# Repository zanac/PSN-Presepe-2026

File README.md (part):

<p align="center"><b>🇬🇧 English</b> &nbsp;·&nbsp; <a href="README.it.md">🇮🇹 Italiano</a></p>

# PSN-Presepe

Arduino Mega 2560 controller for a modular 12 V nativity scene (*presepe*).

It runs a day/night cycle: **GIORNO → TRAMONTO → CREPUSCOLO → NOTTE → ALBA** (day → sunset → dusk → night → dawn). The cycle drives:

- three analog 12 V RGB strips: main sky, sunset side and dawn side;
- two addressable WS2811 chains of twinkling stars, STELLE_01 and STELLE_02 (for example two zones of the sky);
- 16 relays for motors, pumps and lamps.

Every scenography parameter can be changed from a `PRESEPE.INI` file on a microSD card, read at power-on.

This repository holds the complete project, for both board revisions:

- the PCB (KiCad), with the scripts that generate and verify it;
- manufacturing files ready for a turnkey assembler;
- the firmware, with its tests;
- wiring documentation for building the controller on a breadboard without the PCB.

> **Status.** The Rev D PCB was ordered from PCBWay (turnkey assembly, see [manufacturing/pcbway-order-2026-10-04](hardware/rev-d/manufacturing/pcbway-order-2026-10-04/README.md)) and the assembled boards have been tested: everything works. **Rev E** (small fixes plus a status LED and test points, same size and connectors, same firmware) is being designed in [`hardware/rev-e`](hardware/rev-e); it has not been ordered yet. See [Rev E](#rev-e-next-revision).

**Two board releases.** Both use the same firmware, the same `PRESEPE.INI` and the same terminals, so the rest of this README applies to either:

| Release | Folder | State | Use it for |
|---|---|---|---|
| **Rev D** | [`hardware/rev-d`](hardware/rev-d) | ordered, assembled and tested: works | the boards already built; reference for reorders as they are |
| **Rev E** | [`hardware/rev-e`](hardware/rev-e) | designed and verified, not ordered yet | the next order: buzzer footprint for the CEM-1203(42), polarised C1, 8 mil spacing, status LED, test points |

To flash the firmware (plain Mega or Mega + WiFi) see [Step by step with the Arduino IDE](#step-by-step-with-the-arduino-ide).

## Contents

1. [Repository layout](#1-repository-layout)
2. [How the controller works](#2-how-the-controller-works)
3. [The Rev D board](#3-the-rev-d-board)
4. [Board connectors (terminal pinout)](#4-board-connectors-terminal-pinout)
5. [Arduino Mega pin map](#5-arduino-mega-pin-map)
6. [Power, currents and fusing](#6-power-currents-and-fusing)
7. [Wiring the loads](#7-wiring-the-loads)
8. [Breadboard / prototype build without the PCB](#8-breadboard--prototype-build-without-the-pcb)
9. [Firmware](#9-firmware)
10. [SD-card configuration (PRESEPE.INI)](#10-sd-card-configuration-presepeini)
11. [PCB design rules and verification](#11-pcb-design-rules-and-verification)
12. [Ordering the board](#12-ordering-the-board)
13. [Rebuilding everything](#13-rebuilding-everything)
14. [Known limitations and open points](#14-known-limitations-and-open-points)
15. [Safety](#15-safety)
16. [Revision history](#16-revision-history)

---

## 1. Repository layout

```
build.sh                        one-command rebuild + verification of every PCB revision and the firmware
hardware/
  rev-d/                        Rev D, the board ordered from PCBWay (frozen; rebuilds to identical Gerbers)
    build.sh                    rebuild + verification of this revision only
    build/
      scripts/                  PCB generator, router glue, DRC, independent checkers, exporters
      data/                     reference netlist/pad data and the stored routing session (routing.ses)
      lib/PSN_RevD.pretty/      custom footprints (Arduino Mega shield, JLC tooling hole)
    kicad/                      KiCad 7 project: board, rules, schematic (+PDF), local footprint library
    manufacturing/              Gerbers, drill maps, BOMs, pick-and-place files, assembly instructions, 1:1 print
      pcbway-order-2026-10-04/  FROZEN copy of the files actually sent to PCBWay (+ SHA256SUMS, order notes)
    previews/                   renders of the board (KiCad layers and photo-style Gerber renders)
    reports/                    DRC, independent board/Gerber checks, schematic parity, footprint checks
  rev-e/                        Rev E, the next revision (same layout as rev-d; not ordered yet)
firmware/
  PSN-Presepe/                  the whole firmware in one sketch (PSN-Presepe.ino), example PRESEPE.INI, prebuilt HEX, Windows flasher
  PSN-Presepe-WiFi/             firmware of the ESP8266 on a "Mega + WiFi R3" board (web pages, OTA), prebuilt BIN
  web/                          pannello.html, the control panel served by the ESP8266
  tools/                        fw_compile.sh, esp_compile.sh, flash.sh (Linux/macOS), build_web.py, embed_ini.py, run_tests.sh, host tests
    e2e/                        end-to-end test: real Mega link code + real ESP sketch over a lossy simulated serial line
simulation/                     Wokwi simulation of the Rev D wiring (diagram, custom RGB chip, bundle script)
simulation_web/                 browser simulator of the PRESEPE.INI light cycle (open index.html)
demo/                           the WiFi web pages with a simulated board, to try them without hardware (generated)
.github/workflows/firmware.yml  CI: host tests + compile of both firmwares
```

Everything in `hardware/rev-d/kicad/`, `manufacturing/` (except the frozen order folder), `previews/` and `reports/` is generated by `hardware/rev-d/build.sh`. Edit the scripts, not the generated files (see [section 13](#13-rebuilding-everything)).

## 2. How the controller works

| Element | Hardware | Behaviour |
|---|---|---|
| **CIELO** (sky) | 12 V common-anode RGB strip, 3 PWM MOSFET channels | Warm day light, full white at mid-day, fades to dark at night, warm dawn glow |
| **TRAMONTO** (sunset, left) | 12 V RGB strip, 3 PWM channels | Orange/red swell during sunset only, completely off otherwise |
| **ALBA** (dawn, right) | 12 V RGB strip, 3 PWM channels | Lighter warm swell during dawn only |
| **STELLE_01** (stars) | 12 V WS2811 chain on D5 (default 50 pixels) | Random stars appear at dusk, twinkle individually at night, fade at dawn |
| **STELLE_02** (stars) | 12 V WS2811 chain on D8 (default 50 pixels) | Same behaviour as STELLE_01, with its own settings: a second zone of the sky |
| **Relays 1–16** | Omron G5Q-1, potential-free COM/NO/NC contacts | Switched on/off at programmable points of each phase |
| **Controls** | START/STOP, NEXT, TEST buttons, speed potentiometer | Pause/resume, jump to next phase, output test, choose 1 of 3 cycle lengths |
| **OLED** | 0.96" SSD1306 128×64 I2C | Phase, progress, cycle length, SD status, test steps (optional) |
| **Buzzer** | passive piezo / magnetic buzzer | Key beeps and a start-up melody (optional) |
| **microSD** | push-push slot on the board edge | `PRESEPE.INI` with all parameters; without a card the built-in defaults are used |

Default phase boundaries, as % of the cycle: TRAMONTO 40 %, CREPUSCOLO 50 %, NOTTE 55 %, ALBA 85 %. ALBA ends at 100 %, where the next GIORNO begins.

Default cycle lengths: 1, 3 or 5 minutes, chosen by the potentiometer.

## 3. The Rev D board

- 300 × 180 mm, 2 layers, FR-4 1.6 mm, **2 oz copper**, HASL, tented vias.
- The board is a shield: it plugs onto an **Arduino Mega 2560 R3**, which sits underneath. The Mega headers are mounted on the bottom side.
- All field wiring goes through **5.08 mm screw terminals** on the board edges.
- Single **12 V** input. The Mega is powered through VIN, and the microSD gets its own 3.3 V LDO.

| Block | Parts |
|---|---|
| 12 V input | J1, bulk capacitor C1 470 µF |
| RGB drivers | 9 × IRLZ44N logic-level MOSFETs (Q1–Q9), 100 Ω gate resistor + 100 kΩ pull-down each, low-side switching |
| Relay drivers | 2 × ULN2803A (U1, U2), freewheel diodes inside (COM pin to +12 V), 16 × Omron G5Q-1 DC12 |
| Relay outputs | JR1–JR16, 3-pole COM / NO / NC, isolated 230 V AC area (see [section 11](#11-pcb-design-rules-and-verification)) |
| microSD | Hirose DM3AT-SF-PEJM5 push-push with card detect, AMS1117-3.3 LDO from +12 V, 74LVC125A level shifter for SCK/MOSI/CS, 10 kΩ pull-ups |
| Buzzer | BZ1 (passive, 7.6 mm pitch) through 220 Ω from D6 |
| Controls / OLED / pot | Terminals only; the parts are off-board |

| Top (copper + silk) | Bottom (copper + silk) |
|---|---|
|  |  |

Assembly drawing: [previews/PSN-Presepe-Mega-RevD-assembly.png](hardware/rev-d/previews/PSN-Presepe-Mega-RevD-assembly.png). Schematic: [kicad/PSN-Presepe-Mega-RevD-schematic.pdf](hardware/rev-d/kicad/PSN-Presepe-Mega-RevD-schematic.pdf). The schematic is generated from the board and uses global net labels, so read it together with the tables below.

### Rev E (next revision)

Rev E keeps the Rev D board outline, connectors, placement and pin map, so the same firmware runs on both. Files: [`hardware/rev-e`](hardware/rev-e) (`kicad/`, `manufacturing/`, `previews/`, `reports/`, rebuilt by `hardware/rev-e/build.sh`). Status: designed and verified by the same automated checks as Rev D, **not ordered yet**.

| Change | Why |
|---|---|
| BZ1 footprint with **6.5 mm** pin pitch (local footprint `Buzzer_12x9.5RM6.5`) | fits the buzzer PCBWay sources, Same Sky CEM-1203(42); on Rev D they had to bend its pins |
| C1 on a **polarised** footprint (`CP_Radial_D10.0mm_P5.00mm`: square + pad, "+" on the silkscreen) | Rev D had two identical round pads |
| Minimum copper clearance **0.22 mm** (Rev D rule 0.20 mm, 0.202 mm measured) | PCBWay asks for 8 mil (0.2032 mm) with 2 oz copper |
| **Status LED** D1 (green, 3 mm) with RLED 1 kΩ (0805) on Mega D13, top-left next to the microSD | shows at a glance whether the controller runs, is paused, in TEST or STOP (see [Operation](#operation)) |
| **Test points** TP1–TP5 in a row: +12V, GND, +5V, GND, +3V3 (plated 2 mm pads, no part) | measure the supplies with a meter without looking for a pin; a slipping probe can only short a rail to GND, never 12 V onto 5 V |
| No vias above the Mega USB-B socket (rule area in the board, used by the router and by KiCad DRC) | was only checked afterwards on Rev D |
| Star terminals named **J_STELLE_01** / **J_STELLE_02** (silkscreen STELLE_01 / STELLE_02, nets `D5_STELLE_01_DATA` / `D8_STELLE_02_DATA`) | the firmware drives two identical star chains; Rev D still says STELLE / CASETTE |

The routing is new (Freerouting), stored in `hardware/rev-e/build/data/routing.ses` so that the build is reproducible. Before ordering, print the 1:1 PDF and check the real buzzer, C1 and LED on it ([Before ordering a new revision](#before-ordering-a-new-revision)).

## 4. Board connectors (terminal pinout)

Pin 1 is the square pad. The function of each pin is also printed on the silkscreen next to every terminal.

### Bottom edge, left to right

| Terminal | Pin 1 | Pin 2 | Pin 3 | Pin 4 | Use |
|---|---|---|---|---|---|
| **J1** POWER 12V | +12 V | GND | | | Power supply input |
| **J_OLED** | +5 V (Mega) | GND | SDA (D20) | SCL (D21) | OLED display |
| **J_START** | D22 | GND | | | START/STOP button (normally open) |
| **J_NEXT** | D23 | GND | | | NEXT button (normally open) |
| **J_TEST** | D24 | GND | | | TEST button (normally open) |
| **J_POT** | +5 V (Mega) | A0 (wiper) | GND | | External 10 kΩ linear potentiometer |
| **J_CIELO** | +12 V | R− | G− | B− | Sky RGB strip (common anode) |
| **J_TRAMONTO** | +12 V | R− | G− | B− | Sunset RGB strip |
| **J_ALBA** | +12 V | R− | G− | B− | Dawn RGB strip |
| **J_STELLE** (Rev D) / **J_STELLE_01** (Rev E) | +12 V | GND | DATA (D5) | | WS2811 chain STELLE_01 |
| **J_CASETTE** (Rev D) / **J_STELLE_02** (Rev E) | +12 V | GND | DATA (D8) | | WS2811 chain STELLE_02 (the Rev D silkscreen still says CASETTE) |

### Top and right edges (relay area)

| Terminal | Pin 1 | Pin 2 | Pin 3 |
|---|---|---|---|
| **JR1 … JR16** | COM | NO (closed when the relay is on) | NC (closed when the relay is off) |

JR1–JR8 run along the top edge and JR9–JR16 down the right edge. Relay *n* is driven by Mega pin D(24+*n*): relay 1 = D25 … relay 16 = D40.

**microSD (J_SD)** sits on the top edge at x ≈ 95 mm. The card goes in from the board edge and sticks out about 4–5 mm when inserted, so an enclosure needs a slot there.

## 5. Arduino Mega pin map

| Mega pin | Function | Notes |
|---|---|---|
| D2, D3, D4 | CIELO R, G, B (PWM) | Q1–Q3. D4 uses Timer0, so it is 8-bit PWM only |
| D5 | STELLE_01 WS2811 data | |
| D6 | Buzzer | through RBZ1 220 Ω |
| D7, D11, D12 | TRAMONTO R, G, B (PWM) | Q4–Q6, 16-bit timers |
| D8 | STELLE_02 WS2811 data | |
| D20 / D21 | I2C SDA / SCL | OLED address 0x3C |
| D22, D23, D24 | START, NEXT, TEST | `INPUT_PULLUP`; a button shorts the pin to GND |
| D25 … D40 | Relays 1 … 16 | HIGH = relay on (through the ULN2803A) |
| D44, D45, D46 | ALBA R, G, B (PWM) | Q7–Q9, 16-bit timer |
| D49 | microSD card detect | LOW = card inserted (shown on the serial log only) |
| D50 / D51 / D52 / D53 | microSD MISO / MOSI / SCK / CS | hardware SPI |
| A0 | Speed potentiometer | |
| VIN | +12 V from the board | the Mega is powered through the shield |
| 5V | to J_OLED / J_POT only | |

| D13 | Status LED | Rev E: green LED D1 through RLED 1 kΩ. Rev D: only the Mega's own "L" LED (under the shield) |
| D14 / D15 | Serial3 TX3 / RX3 | link to the ESP8266 of a "Mega + WiFi R3" board (no track on the PCB) |

Free pins: D9, D10, D16–D19, D41–D43, D47, D48, A1–A15. D9 and D10 can also do PWM.

## 6. Power, currents and fusing

- **Supply:** one 12 V DC switching power supply. Size it from the sum of:
  - the RGB strips at full white;
  - the WS2811 chains (up to roughly 0.7 W per pixel at full white for common 12 V WS2811 strings; check yours);
  - the relay coils (all 16 on < 0.6 A);
  - the Mega with OLED (≈ 0.1 A).
- **Fuse** the 12 V supply output at no more than **8 A**. The 3 mm, 2 oz +12 V / GND trunks carry about 9 A with a 10 °C temperature rise.
- **RGB channels:** each colour channel is a 1.5 mm, 2 oz trace through an IRLZ44N. Keep each channel at **4 A or less**. A typical 1 m 5050 RGB strip uses about 0.4 A per colour.
- **Relay contacts:** NO contact 10 A / 250 V AC resistive, NC contact only 3 A / 250 V AC (Omron G5Q-1 rating). Put heavy loads on COM–NO. The contact traces are doubled on both layers (2 mm, 2 oz each), so the relay is the limit, not the copper.
  - Motors and other inductive loads draw an inrush current: keep a good margin.
  - DC loads above about 30 V are not recommended, because DC arcs are hard for these contacts to break.
- **Small-signal loads:** the G5Q-1 has power contacts with silver alloy, made to switch amperes. Very small currents, such as logic inputs (a few mA), are not switched reliably. Use a signal relay with gold contacts for those; see the Omron datasheet for the minimum load.
- **Mega supply:** the Mega regulates the 12 V on VIN down to 5 V. Only the OLED and the potentiometer use that 5 V, so its regulator stays cool. **Never connect +12 V to the Mega 5V pin or to any I/O pin.**
- **USB and 12 V together are fine:** the Mega switches between its power sources automatically. With USB only, the Mega, OLED and potentiometer work. The relays, strips and microSD have no power, because they run from 12 V.

## 7. Wiring the loads

### Analog RGB strips (CIELO / TRAMONTO / ALBA)

The strips are **common-anode** (common +12 V). The board switches the negative R, G and B returns.

```
J_CIELO pin 1 (+12 V) ──► strip +12V (common)
J_CIELO pin 2 (R−)    ──► strip R
J_CIELO pin 3 (G−)    ──► strip G
J_CIELO pin 4 (B−)    ──► strip B
```

Do not connect a strip's R/G/B to +12 V or GND directly.

### WS2811 chains (STELLE_01 / STELLE_02)

```
J_STELLE_01 pin 1 (+12 V) ──► chain +12V
J_STELLE_01 pin 2 (GND)   ──► chain GND
J_STELLE_01 pin 3 (DATA)  ──[330 Ω, recommended, at the chain input]──► chain DIN
```

J_STELLE_02 is wired the same way. On the Rev D board the two terminals are labelled STELLE and CASETTE.

The board has no series resistor on DATA. Put a 330–470 Ω resistor in the data wire, close to the first pixel. This matters most with long wires.

For long chains, also feed +12 V at the far end of the chain. Set the number of pixels in `[STELLE_01] numero` and `[STELLE_02] numero`. The maximum is 100 per chain; 0 leaves a chain unused.

### Relays (potential-free contacts)

Each relay is an independent changeover contact, so every relay can switch a different circuit. For example, relay 1 can switch 230 V AC while relay 2 switches a 12 V pump.

Inside one relay, COM, NO and NC must belong to the **same** circuit.

Example: a 230 V AC motor on relay 1.

```
Mains L (phase, brown) ──► JR1 pin 1 COM
JR1 pin 2 NO ────────────► motor wire 1
Mains N (neutral, blue) ─► motor wire 2           (does not go through the board)
Mains PE (green/yellow) ─► motor earth, if any    (does not go through the board)
```

If the Arduino resets or misbehaves when a motor switches off, fit an RC snubber across the motor: 100 Ω + 100 nF, X2-rated for 250 V AC.

### Buttons, potentiometer, OLED

- **Buttons:** normally-open push buttons between each Dxx terminal pin and the GND pin next to it. No resistors are needed.
- **Potentiometer:** 10 kΩ linear (B10K). One end to pin 1 (+5 V), wiper to pin 2 (A0), other end to pin 3 (GND). If the knob turns the "wrong" way, set `[CICLO] pot_invertito`.
- **OLED:** an SSD1306 128×64 I2C module at address 0x3C, wired 5 V / GND / SDA / SCL.
  - Module pin orders differ: some are VCC-GND-SCL-SDA, others GND-VCC-SCL-SDA. Check the labels printed on your module.
  - Keep the I2C cable under about 1 m.

## 8. Breadboard / prototype build without the PCB

Every block of the PCB can be rebuilt on a breadboard or perfboard with the same Mega pins, so the same firmware runs unchanged. Common rules:

- One 12 V supply for the loads.
- The Mega is powered from USB or from 12 V on VIN.
- **Arduino GND and the 12 V supply 0 V must be connected together.** This common ground is required for the WS2811 data and the MOSFET gates.

### 8.1 One RGB colour channel (repeat 9 times)

Pins: D2/D3/D4 for CIELO, D7/D11/D12 for TRAMONTO, D44/D45/D46 for ALBA.

```
Mega Dx ──[100 Ω]──┬──► Gate   IRLZ44N  (TO-220 pinout: G - D - S, seen from the front)
                   │
                [100 kΩ]
                   │
GND ───────────────┴──► Source
Drain ───────────────► strip colour wire (R−, G− or B−)
+12 V ───────────────► strip common +12V
```

You can use ready-made MOSFET modules instead. If a module is active-low, set `[COLORI] pwm_invertito = 1`.

### 8.2 Relays

On the PCB, a ULN2803A sinks the coil current, and its internal diodes clamp the coil when it switches off:

```
Mega D25..D32 ──► ULN2803A #1 inputs 1..8 (pins 1..8)      Mega D33..D40 ──► ULN2803A #2 inputs 1..8
ULN2803A pin 9 = GND, pin 10 (COM) = +12 V
ULN2803A output n (pin 19-n) ──► relay coil −         relay coil + ──► +12 V
```

With off-the-shelf 4- or 8-channel relay modules, connect IN1…IN16 to D25…D40. Most modules are **active-low**: set `[RELE] logica = bassa` in `PRESEPE.INI`. Power the module coils from a suitable supply, not from the Mega 5 V pin.

### 8.3 WS2811 chains

```
Mega D5 ──[330 Ω]──► STELLE_01 DIN     Mega D8 ──[330 Ω]──► STELLE_02 DIN
12 V supply + / 0 V ──► chain +12V / GND, with 0 V common with Arduino GND
```

### 8.4 Controls, OLED, buzzer

```
D22 ──[START]── GND      D23 ──[NEXT]── GND      D24 ──[TEST]── GND
+5V ── pot end   A0 ── pot wiper   GND ── pot other end
OLED: VCC → 5V, GND → GND, SDA → D20, SCL → D21
D6 ──[220 Ω]──► passive buzzer + ; buzzer − ──► GND     (optional)
```

### 8.5 microSD

Use a standard 5 V "microSD card adapter" module, the kind with its own 3.3 V regulator and level shifter. A bare 3.3 V breakout without a level shifter will be damaged.

```
module VCC → 5V    GND → GND    MISO → D50    MOSI → D51    SCK → D52    CS → D53
```

Card detect (D49) is optional. If the module has no CD pin, leave D49 unconnected. The firmware only uses CD for the serial log, and it decides whether a card is present by trying to read it.

## 9. Firmware

Source: **one file**, `firmware/PSN-Presepe/PSN-Presepe.ino` (comments in Italian). Target: Arduino Mega 2560. The same file is compiled by the Arduino IDE, by `arduino-cli` and by Wokwi. The `PRESEPE.INI` reader sits between the `// ==== CONFIG BEGIN ====` and `// ==== CONFIG END ====` markers; `firmware/tools/run_tests.sh` extracts that block and tests it on a PC.

Libraries: Adafruit NeoPixel, Adafruit GFX, Adafruit SSD1306 (with Adafruit BusIO), Arduino SD; SPI and Wire come with the core. Versions used for the current HEX:

| Library | Version |
|---|---|
| NeoPixel | 1.15.5 |
| GFX | 1.12.6 |
| SSD1306 | 2.5.17 |
| BusIO | 1.17.4 |
| SD | 1.3.0 |

Size: 95.7 kB flash (37 %, of which 17.6 kB is the embedded default `PRESEPE.INI`), 5.2 kB static RAM. That leaves about 3.0 kB for heap and stack; the OLED buffer (1 kB) and the LED buffers (3 bytes per pixel) are allocated at run time, after which about 1.7 kB stay free.

### Build

- **Arduino IDE:** open `firmware/PSN-Presepe/PSN-Presepe.ino`, select *Arduino Mega or Mega 2560*, then Upload.
- **Command line:**

  ```sh
  arduino-cli core install arduino:avr
  arduino-cli lib install "Adafruit NeoPixel" "Adafruit GFX Library" "Adafruit SSD1306" "SD"
  firmware/tools/fw_compile.sh                       # -> firmware/PSN-Presepe/build/PSN-Presepe.ino.hex
  firmware/tools/esp_compile.sh                      # ESP8266 firmware (needs the esp8266 core, see WiFi below)
  firmware/tools/run_tests.sh                        # INI reader, colour mode, WiFi link, ESP <-> Mega end-to-end
  ```

The sketch declares its prototypes explicitly, so it does not depend on the IDE's automatic prototype generation.

### Flash the prebuilt HEX

- **Windows:** copy `PSN-Presepe.ino.hex` and `flash-windows.bat` into one folder and run the BAT. It downloads arduino-cli on first use and auto-detects an original Mega; with a CH340 clone (WeMos and others) it asks for the COM port.
- **Linux / macOS:** `firmware/tools/flash.sh [port]`.

Flash with the 12 V supply off: during the upload the outputs toggle, and without 12 V no relay can switch. The Mega can stay plugged into the board, as long as the USB plug fits ([section 14](#14-known-limitations-and-open-points)).

### Step by step with the Arduino IDE

The same firmware runs on both board revisions (Rev D and Rev E) and on either controller:

- **Arduino Mega 2560** (original or clone): only the Mega firmware, parts A and B.
- **"Mega + WiFi R3"** (WeMos / RobotDyn, ATmega2560 + ESP8266 on one board, CH340 USB chip): both firmwares, parts A and C.

Download the repository (*Code → Download ZIP* on GitHub) and unpack it into a **new, empty folder**. An old sketch folder with leftover files (for example a former `PresepeConfig.cpp`) breaks the build with *multiple definition* errors.

**A. Once: Arduino IDE, libraries, ESP8266 package**

1. Install the Arduino IDE 2.x from arduino.cc.
2. *Tools → Manage Libraries*: install **Adafruit NeoPixel**, **Adafruit GFX Library**, **Adafruit SSD1306** (answer *Install all* to add Adafruit BusIO) and check that **SD** (by Arduino) is installed.
3. Only for the WiFi board: *File → Preferences → Additional boards manager URLs*, add `https://arduino.esp8266.com/stable/package_esp8266com_index.json`; then *Tools → Board → Boards Manager*, install **esp8266** (by ESP8266 Community) version **3.1.2**.
4. Clones with a CH340 USB chip (the WeMos and many Megas) need the CH340 driver on Windows: the board must appear in *Device Manager → Ports* as "USB-SERIAL CH340 (COMx)".

**B. Arduino Mega 2560**

1. Connect the Mega by USB. If it is already on the shield, switch the 12 V supply off.
2. Open `firmware/PSN-Presepe/PSN-Presepe.ino`. Only one tab must appear.
3. *Tools → Board → Arduino AVR Boards → Arduino Mega or Mega 2560*, *Processor: ATmega2560*, *Port*: the Mega's COM port.
4. **Upload**. The IDE reports about 88 kB (34 %) of program storage.
5. Check: *Serial Monitor* at **115200 baud** prints the configuration at start-up.

**C. "Mega + WiFi R3" board (two firmwares)**

The DIP switches sit under the shield once the board is mounted: do C1–C3 with the board off the shield, powered by USB only, and **always unplug the USB before moving a DIP switch**.

*C1 – Mega firmware*
1. DIP **3 and 4 ON**, all others OFF. Plug in the USB.
2. As in part B: open `PSN-Presepe.ino`, board *Arduino Mega or Mega 2560*, the CH340 COM port, **Upload**.

*C2 – ESP8266 firmware*
1. Unplug the USB. DIP **5, 6 and 7 ON**, all others OFF (DIP 7 puts the ESP8266 in flash mode). Plug in the USB.
2. Open `firmware/PSN-Presepe-WiFi/PSN-Presepe-WiFi.ino`. Two tabs appear: the sketch and `pagine_web.h` (the web pages, generated; it must stay in the same folder).
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
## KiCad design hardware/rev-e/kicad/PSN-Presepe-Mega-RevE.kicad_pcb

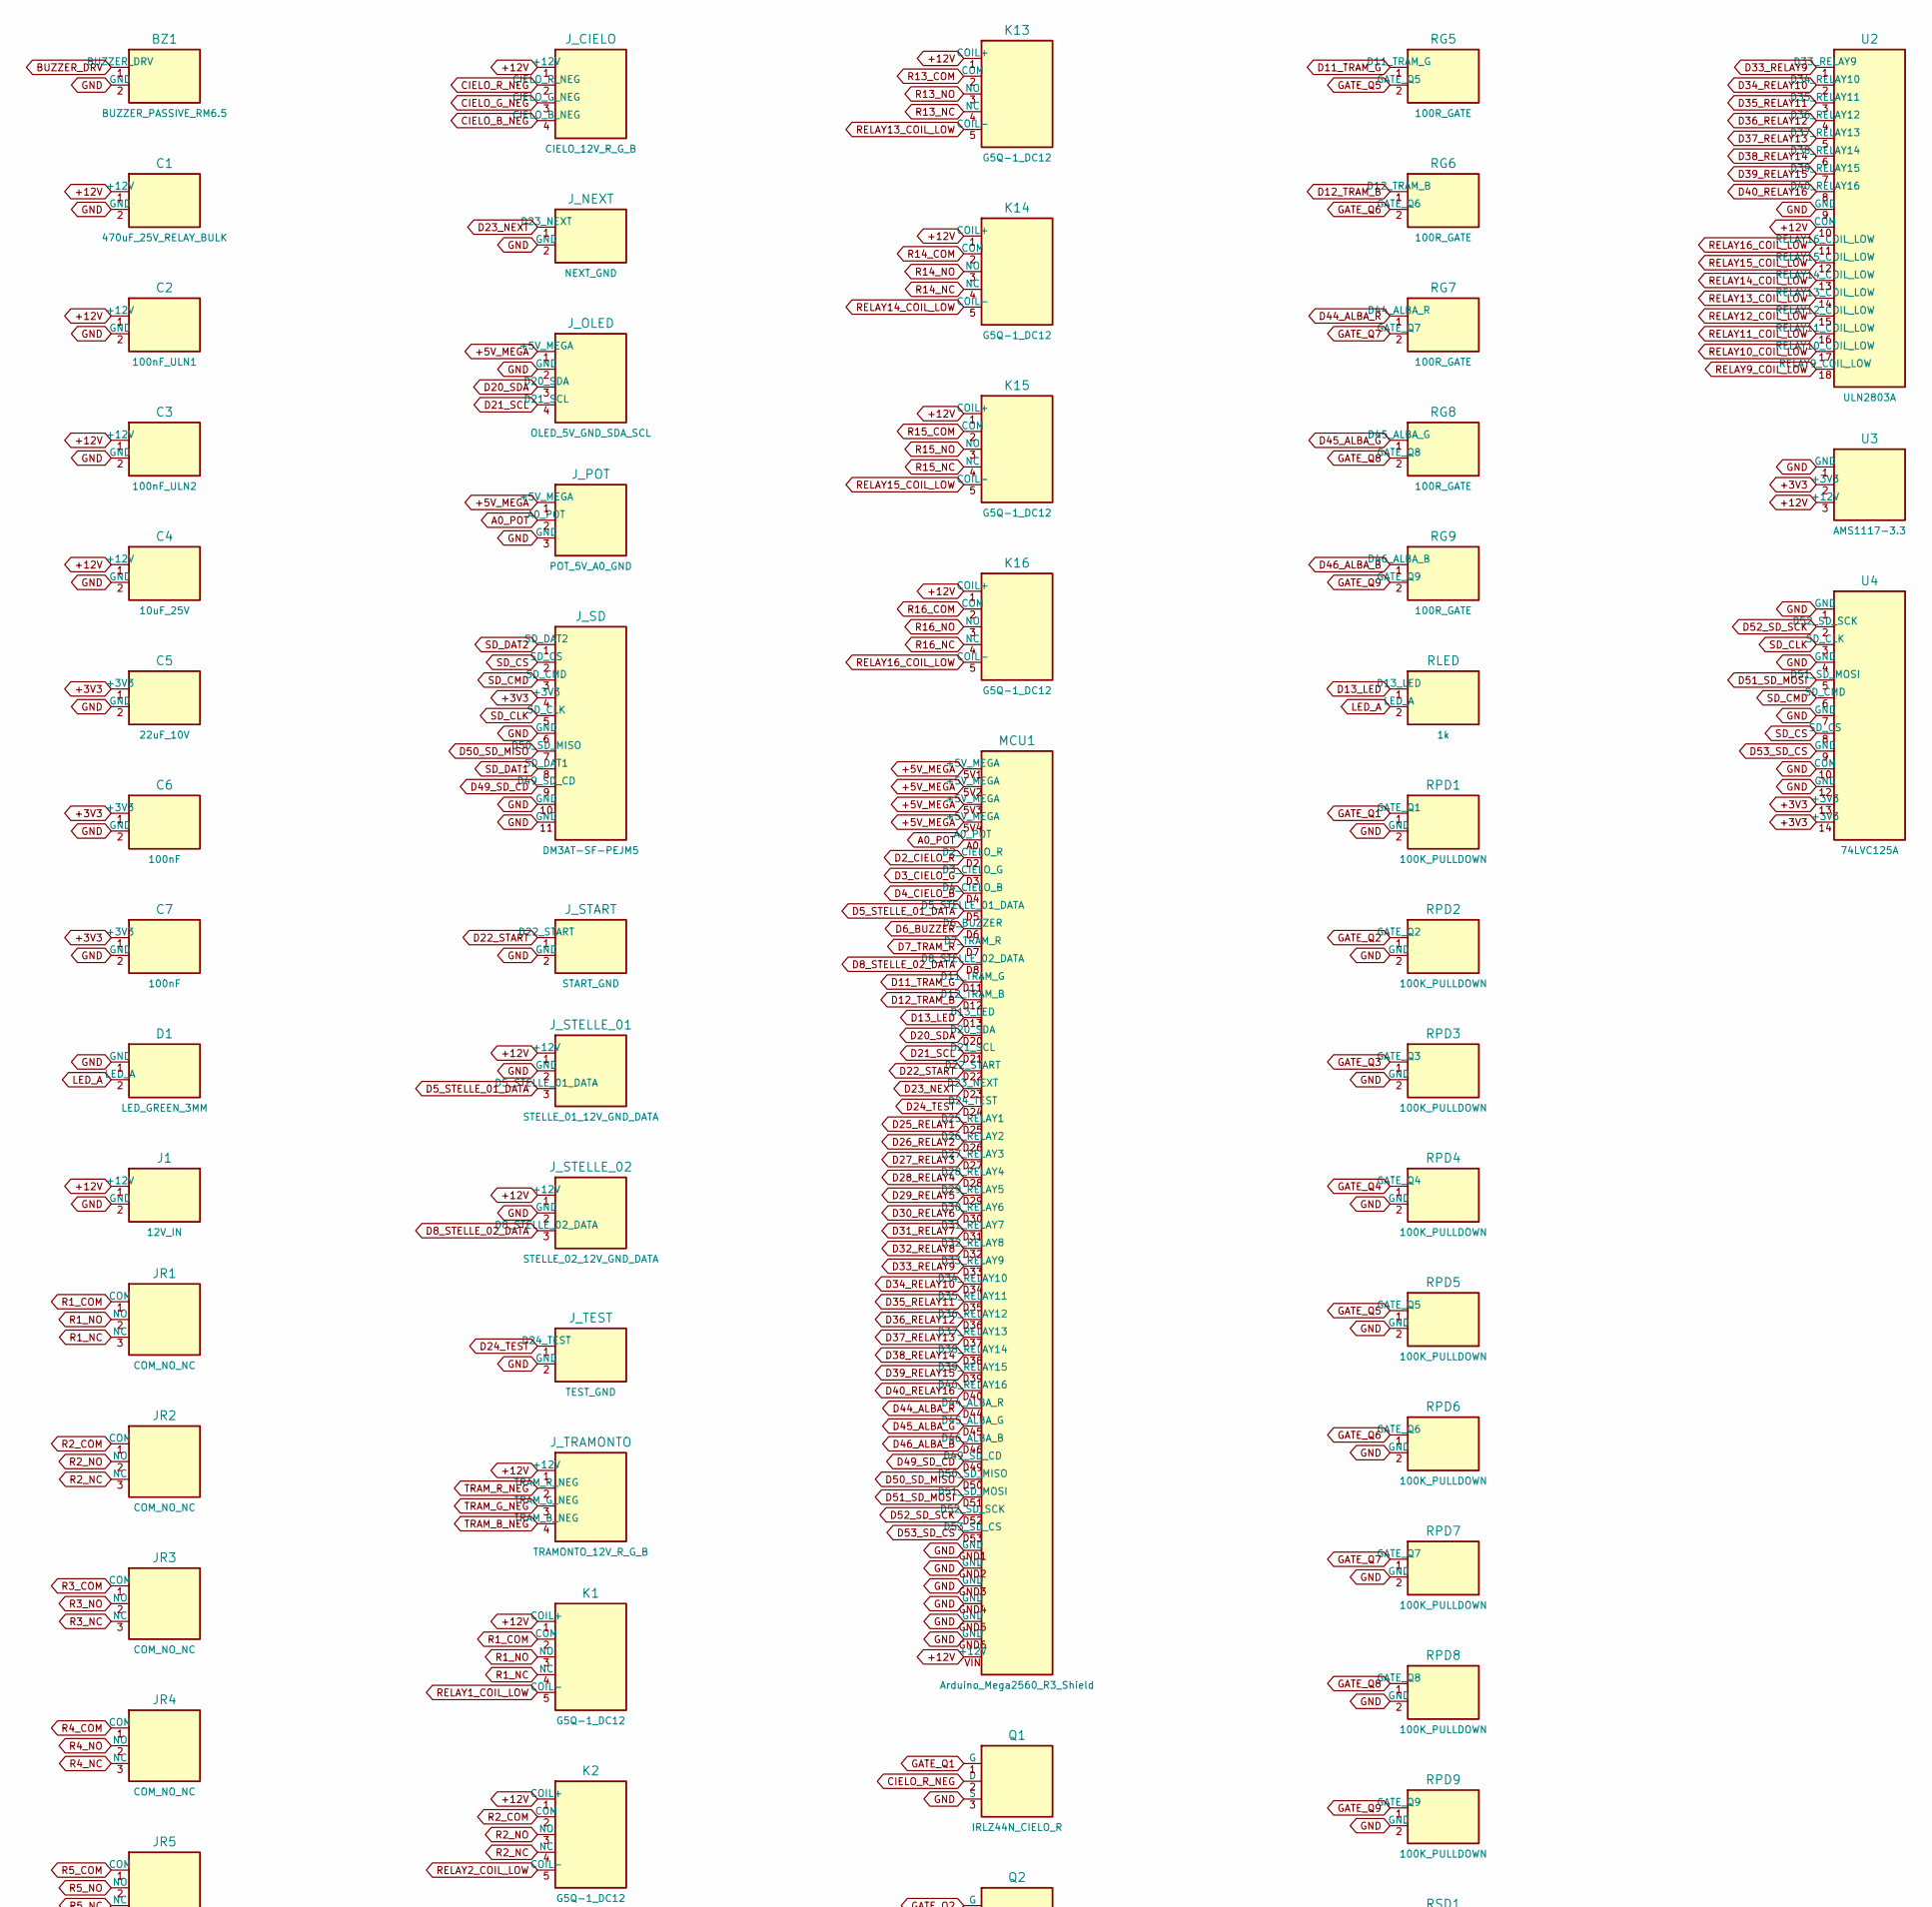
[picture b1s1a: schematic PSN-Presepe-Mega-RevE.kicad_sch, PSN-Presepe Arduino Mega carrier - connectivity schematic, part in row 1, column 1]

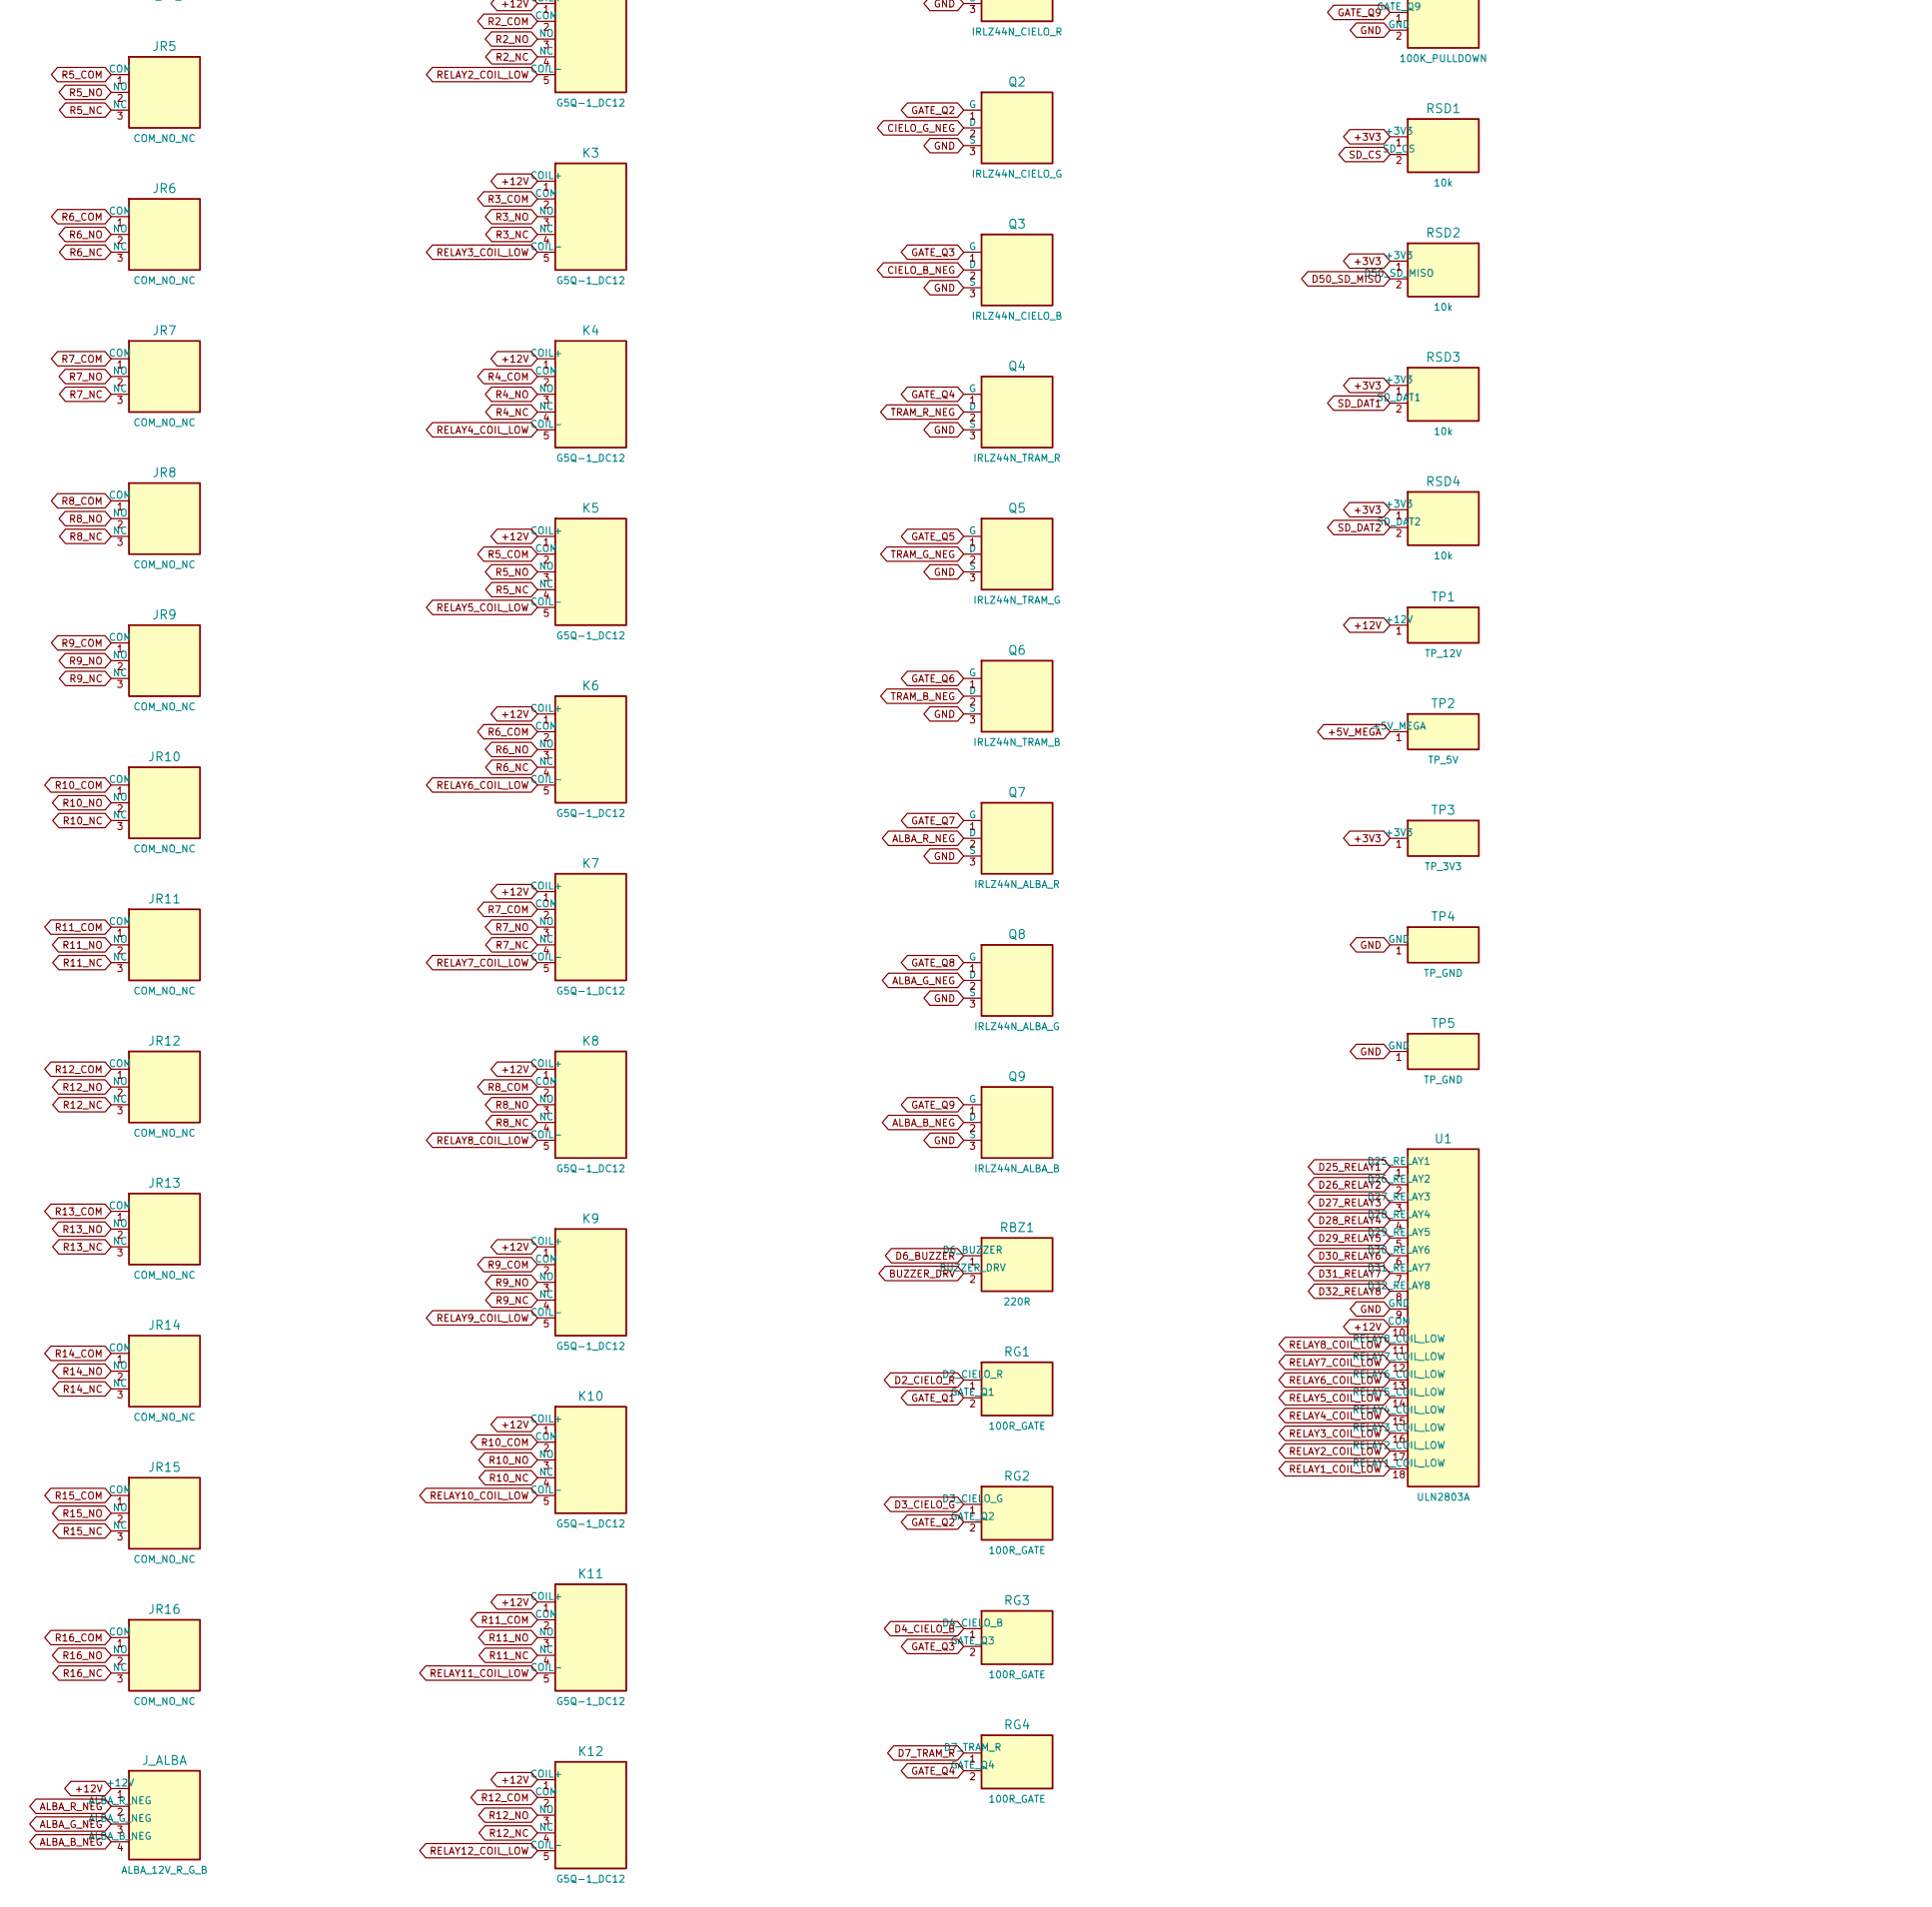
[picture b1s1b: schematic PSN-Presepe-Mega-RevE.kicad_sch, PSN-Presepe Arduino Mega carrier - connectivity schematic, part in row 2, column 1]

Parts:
BZ1: BUZZER_PASSIVE_RM6.5; Buzzer_12x9.5RM6.5
C1: 470uF_25V_RELAY_BULK; CP_Radial_D10.0mm_P5.00mm
C2: 100nF_ULN1; C_Disc_D5.0mm_W2.5mm_P5.00mm
C3: 100nF_ULN2; C_Disc_D5.0mm_W2.5mm_P5.00mm
C4: 10uF_25V; C_0805_2012Metric
C5: 22uF_10V; C_0805_2012Metric
C6, C7: 100nF; C_0805_2012Metric
D1: LED_GREEN_3MM; LED_D3.0mm
J1: 12V_IN; TerminalBlock_Phoenix_MKDS-1,5-2-5.08_1x02_P5.08mm_Horizont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
JR1, JR2, JR3, JR4, JR5, JR6, JR7, JR8, JR9, JR10, JR11, JR12, JR13, JR14, JR15, JR16: COM_NO_NC; TerminalBlock_Phoenix_MKDS-1,5-3-5.08_1x03_P5.08mm_Horizont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
J_ALBA: ALBA_12V_R_G_B; TerminalBlock_Phoenix_MKDS-1,5-4-5.08_1x04_P5.08mm_Horizont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
J_CIELO: CIELO_12V_R_G_B; TerminalBlock_Phoenix_MKDS-1,5-4-5.08_1x04_P5.08mm_Horizont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
J_NEXT: NEXT_GND; TerminalBlock_Phoenix_MKDS-1,5-2-5.08_1x02_P5.08mm_Horizont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
J_OLED: OLED_5V_GND_SDA_SCL; TerminalBlock_Phoenix_MKDS-1,5-4-5.08_1x04_P5.08mm_Horizont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
J_POT: POT_5V_A0_GND; TerminalBlock_Phoenix_MKDS-1,5-3-5.08_1x03_P5.08mm_Horizont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
J_SD: DM3AT-SF-PEJM5; microSD_HC_Hirose_DM3AT-SF-PEJM5
J_START: START_GND; TerminalBlock_Phoenix_MKDS-1,5-2-5.08_1x02_P5.08mm_Horizont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
J_STELLE_01: STELLE_01_12V_GND_DATA; TerminalBlock_Phoenix_MKDS-1,5-3-5.08_1x03_P5.08mm_Horizont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
J_STELLE_02: STELLE_02_12V_GND_DATA; TerminalBlock_Phoenix_MKDS-1,5-3-5.08_1x03_P5.08mm_Horizont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
J_TEST: TEST_GND; TerminalBlock_Phoenix_MKDS-1,5-2-5.08_1x02_P5.08mm_Horizont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
J_TRAMONTO: TRAMONTO_12V_R_G_B; TerminalBlock_Phoenix_MKDS-1,5-4-5.08_1x04_P5.08mm_Horizont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
K1, K2, K3, K4, K5, K6, K7, K8, K9, K10, K11, K12, K13, K14, K15, K16: G5Q-1_DC12; Relay_SPDT_Omron-G5Q-1
MCU1: Arduino_Mega2560_R3_Shield
Q1: IRLZ44N_CIELO_R; TO-220-3_Vertical
Q2: IRLZ44N_CIELO_G; TO-220-3_Vertical
Q3: IRLZ44N_CIELO_B; TO-220-3_Vertical
Q4: IRLZ44N_TRAM_R; TO-220-3_Vertical
Q5: IRLZ44N_TRAM_G; TO-220-3_Vertical
Q6: IRLZ44N_TRAM_B; TO-220-3_Vertical
Q7: IRLZ44N_ALBA_R; TO-220-3_Vertical
Q8: IRLZ44N_ALBA_G; TO-220-3_Vertical
Q9: IRLZ44N_ALBA_B; TO-220-3_Vertical
RBZ1: 220R; R_Axial_DIN0207_L6.3mm_D2.5mm_P10.16mm_Horizontal
RG1, RG2, RG3, RG4, RG5, RG6, RG7, RG8, RG9: 100R_GATE; R_Axial_DIN0207_L6.3mm_D2.5mm_P10.16mm_Horizontal
RLED: 1k; R_0805_2012Metric
RPD1, RPD2, RPD3, RPD4, RPD5, RPD6, RPD7, RPD8, RPD9: 100K_PULLDOWN; R_Axial_DIN0207_L6.3mm_D2.5mm_P10.16mm_Horizontal
RSD1, RSD2, RSD3, RSD4: 10k; R_0805_2012Metric
TP1: TP_12V; TestPoint_THTPad_D2.0mm_Drill1.0mm
TP2: TP_5V; TestPoint_THTPad_D2.0mm_Drill1.0mm
TP3: TP_3V3; TestPoint_THTPad_D2.0mm_Drill1.0mm
TP4, TP5: TP_GND; TestPoint_THTPad_D2.0mm_Drill1.0mm
U1, U2: ULN2803A; DIP-18_W7.62mm
U3: AMS1117-3.3; SOT-223-3_TabPin2
U4: 74LVC125A; SOIC-14_3.9x8.7mm_P1.27mm

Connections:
+3V3: C5.1 (+3V3), C6.1 (+3V3), C7.1 (+3V3), J_SD.4 (+3V3), RSD1.1 (+3V3), RSD2.1 (+3V3), RSD3.1 (+3V3), RSD4.1 (+3V3), TP3.1, U3.2 (+3V3), U4.13 (+3V3), U4.14 (+3V3)
+5V_MEGA: J_OLED.1 (+5V_MEGA), J_POT.1 (+5V_MEGA), MCU1.5V1 (+5V_MEGA), MCU1.5V2 (+5V_MEGA), MCU1.5V3 (+5V_MEGA), MCU1.5V4 (+5V_MEGA), TP2.1
+12V: C1.1 (+12V), C2.1 (+12V), C3.1 (+12V), C4.1 (+12V), J1.1 (+12V), J_ALBA.1 (+12V), J_CIELO.1 (+12V), J_STELLE_01.1 (+12V), J_STELLE_02.1 (+12V), J_TRAMONTO.1 (+12V), K1.1 (COIL+), K2.1 (COIL+), K3.1 (COIL+), K4.1 (COIL+), K5.1 (COIL+), K6.1 (COIL+), K7.1 (COIL+), K8.1 (COIL+), K9.1 (COIL+), K10.1 (COIL+), K11.1 (COIL+), K12.1 (COIL+), K13.1 (COIL+), K14.1 (COIL+), K15.1 (COIL+), K16.1 (COIL+), MCU1.VIN (+12V), TP1.1, U1.10 (COM), U2.10 (COM), U3.3 (+12V)
A0_POT: J_POT.2 (A0_POT), MCU1.A0 (A0_POT)
ALBA_B_NEG: J_ALBA.4 (ALBA_B_NEG), Q9.2 (D)
ALBA_G_NEG: J_ALBA.3 (ALBA_G_NEG), Q8.2 (D)
ALBA_R_NEG: J_ALBA.2 (ALBA_R_NEG), Q7.2 (D)
BUZZER_DRV: BZ1.1 (BUZZER_DRV), RBZ1.2 (BUZZER_DRV)
CIELO_B_NEG: J_CIELO.4 (CIELO_B_NEG), Q3.2 (D)
CIELO_G_NEG: J_CIELO.3 (CIELO_G_NEG), Q2.2 (D)
CIELO_R_NEG: J_CIELO.2 (CIELO_R_NEG), Q1.2 (D)
D2_CIELO_R: MCU1.D2 (D2_CIELO_R), RG1.1 (D2_CIELO_R)
D3_CIELO_G: MCU1.D3 (D3_CIELO_G), RG2.1 (D3_CIELO_G)
D4_CIELO_B: MCU1.D4 (D4_CIELO_B), RG3.1 (D4_CIELO_B)
D5_STELLE_01_DATA: J_STELLE_01.3 (D5_STELLE_01_DATA), MCU1.D5 (D5_STELLE_01_DATA)
D6_BUZZER: MCU1.D6 (D6_BUZZER), RBZ1.1 (D6_BUZZER)
D7_TRAM_R: MCU1.D7 (D7_TRAM_R), RG4.1 (D7_TRAM_R)
D8_STELLE_02_DATA: J_STELLE_02.3 (D8_STELLE_02_DATA), MCU1.D8 (D8_STELLE_02_DATA)
D11_TRAM_G: MCU1.D11 (D11_TRAM_G), RG5.1 (D11_TRAM_G)
D12_TRAM_B: MCU1.D12 (D12_TRAM_B), RG6.1 (D12_TRAM_B)
D13_LED: MCU1.D13 (D13_LED), RLED.1 (D13_LED)
D20_SDA: J_OLED.3 (D20_SDA), MCU1.D20 (D20_SDA)
D21_SCL: J_OLED.4 (D21_SCL), MCU1.D21 (D21_SCL)
D22_START: J_START.1 (D22_START), MCU1.D22 (D22_START)
D23_NEXT: J_NEXT.1 (D23_NEXT), MCU1.D23 (D23_NEXT)
D24_TEST: J_TEST.1 (D24_TEST), MCU1.D24 (D24_TEST)
D25_RELAY1: MCU1.D25 (D25_RELAY1), U1.1 (D25_RELAY1)
D26_RELAY2: MCU1.D26 (D26_RELAY2), U1.2 (D26_RELAY2)
D27_RELAY3: MCU1.D27 (D27_RELAY3), U1.3 (D27_RELAY3)
D28_RELAY4: MCU1.D28 (D28_RELAY4), U1.4 (D28_RELAY4)
D29_RELAY5: MCU1.D29 (D29_RELAY5), U1.5 (D29_RELAY5)
D30_RELAY6: MCU1.D30 (D30_RELAY6), U1.6 (D30_RELAY6)
D31_RELAY7: MCU1.D31 (D31_RELAY7), U1.7 (D31_RELAY7)
D32_RELAY8: MCU1.D32 (D32_RELAY8), U1.8 (D32_RELAY8)
D33_RELAY9: MCU1.D33 (D33_RELAY9), U2.1 (D33_RELAY9)
D34_RELAY10: MCU1.D34 (D34_RELAY10), U2.2 (D34_RELAY10)
D35_RELAY11: MCU1.D35 (D35_RELAY11), U2.3 (D35_RELAY11)
D36_RELAY12: MCU1.D36 (D36_RELAY12), U2.4 (D36_RELAY12)
D37_RELAY13: MCU1.D37 (D37_RELAY13), U2.5 (D37_RELAY13)
D38_RELAY14: MCU1.D38 (D38_RELAY14), U2.6 (D38_RELAY14)
D39_RELAY15: MCU1.D39 (D39_RELAY15), U2.7 (D39_RELAY15)
D40_RELAY16: MCU1.D40 (D40_RELAY16), U2.8 (D40_RELAY16)
D44_ALBA_R: MCU1.D44 (D44_ALBA_R), RG7.1 (D44_ALBA_R)
D45_ALBA_G: MCU1.D45 (D45_ALBA_G), RG8.1 (D45_ALBA_G)
D46_ALBA_B: MCU1.D46 (D46_ALBA_B), RG9.1 (D46_ALBA_B)
D49_SD_CD: J_SD.9 (D49_SD_CD), MCU1.D49 (D49_SD_CD)
D50_SD_MISO: J_SD.7 (D50_SD_MISO), MCU1.D50 (D50_SD_MISO), RSD2.2 (D50_SD_MISO)
D51_SD_MOSI: MCU1.D51 (D51_SD_MOSI), U4.5 (D51_SD_MOSI)
D52_SD_SCK: MCU1.D52 (D52_SD_SCK), U4.2 (D52_SD_SCK)
D53_SD_CS: MCU1.D53 (D53_SD_CS), U4.9 (GND)
GATE_Q1: Q1.1 (G), RG1.2 (GATE_Q1), RPD1.1 (GATE_Q1)
GATE_Q2: Q2.1 (G), RG2.2 (GATE_Q2), RPD2.1 (GATE_Q2)
GATE_Q3: Q3.1 (G), RG3.2 (GATE_Q3), RPD3.1 (GATE_Q3)
GATE_Q4: Q4.1 (G), RG4.2 (GATE_Q4), RPD4.1 (GATE_Q4)
GATE_Q5: Q5.1 (G), RG5.2 (GATE_Q5), RPD5.1 (GATE_Q5)
GATE_Q6: Q6.1 (G), RG6.2 (GATE_Q6), RPD6.1 (GATE_Q6)
GATE_Q7: Q7.1 (G), RG7.2 (GATE_Q7), RPD7.1 (GATE_Q7)
GATE_Q8: Q8.1 (G), RG8.2 (GATE_Q8), RPD8.1 (GATE_Q8)
GATE_Q9: Q9.1 (G), RG9.2 (GATE_Q9), RPD9.1 (GATE_Q9)
GND: BZ1.2 (GND), C1.2 (GND), C2.2 (GND), C3.2 (GND), C4.2 (GND), C5.2 (GND), C6.2 (GND), C7.2 (GND), D1.1 (GND), J1.2 (GND), J_NEXT.2 (GND), J_OLED.2 (GND), J_POT.3 (GND), J_SD.6 (GND), J_SD.10 (GND), J_SD.11 (GND), J_START.2 (GND), J_STELLE_01.2 (GND), J_STELLE_02.2 (GND), J_TEST.2 (GND), MCU1.GND1 (GND), MCU1.GND2 (GND), MCU1.GND3 (GND), MCU1.GND4 (GND), MCU1.GND5 (GND), MCU1.GND6 (GND), Q1.3 (S), Q2.3 (S), Q3.3 (S), Q4.3 (S), Q5.3 (S), Q6.3 (S), Q7.3 (S), Q8.3 (S), Q9.3 (S), RPD1.2 (GND), RPD2.2 (GND), RPD3.2 (GND), RPD4.2 (GND), RPD5.2 (GND), RPD6.2 (GND), RPD7.2 (GND), RPD8.2 (GND), RPD9.2 (GND), TP4.1, TP5.1, U1.9 (GND), U2.9 (GND), U3.1 (GND), U4.1 (GND), U4.4 (GND), U4.7 (GND), U4.10 (COM), U4.12 (GND)
LED_A: D1.2 (LED_A), RLED.2 (LED_A)
R1_COM: JR1.1 (COM), K1.2 (COM)
R1_NC: JR1.3 (NC), K1.4 (NC)
R1_NO: JR1.2 (NO), K1.3 (NO)
R2_COM: JR2.1 (COM), K2.2 (COM)
R2_NC: JR2.3 (NC), K2.4 (NC)
R2_NO: JR2.2 (NO), K2.3 (NO)
R3_COM: JR3.1 (COM), K3.2 (COM)
R3_NC: JR3.3 (NC), K3.4 (NC)
R3_NO: JR3.2 (NO), K3.3 (NO)
R4_COM: JR4.1 (COM), K4.2 (COM)
R4_NC: JR4.3 (NC), K4.4 (NC)
R4_NO: JR4.2 (NO), K4.3 (NO)
R5_COM: JR5.1 (COM), K5.2 (COM)
R5_NC: JR5.3 (NC), K5.4 (NC)
R5_NO: JR5.2 (NO), K5.3 (NO)
R6_COM: JR6.1 (COM), K6.2 (COM)
R6_NC: JR6.3 (NC), K6.4 (NC)
R6_NO: JR6.2 (NO), K6.3 (NO)
R7_COM: JR7.1 (COM), K7.2 (COM)
R7_NC: JR7.3 (NC), K7.4 (NC)
R7_NO: JR7.2 (NO), K7.3 (NO)
R8_COM: JR8.1 (COM), K8.2 (COM)
R8_NC: JR8.3 (NC), K8.4 (NC)
R8_NO: JR8.2 (NO), K8.3 (NO)
R9_COM: JR9.1 (COM), K9.2 (COM)
R9_NC: JR9.3 (NC), K9.4 (NC)
R9_NO: JR9.2 (NO), K9.3 (NO)
R10_COM: JR10.1 (COM), K10.2 (COM)
R10_NC: JR10.3 (NC), K10.4 (NC)
R10_NO: JR10.2 (NO), K10.3 (NO)
R11_COM: JR11.1 (COM), K11.2 (COM)
R11_NC: JR11.3 (NC), K11.4 (NC)
R11_NO: JR11.2 (NO), K11.3 (NO)
R12_COM: JR12.1 (COM), K12.2 (COM)
R12_NC: JR12.3 (NC), K12.4 (NC)
R12_NO: JR12.2 (NO), K12.3 (NO)
R13_COM: JR13.1 (COM), K13.2 (COM)
R13_NC: JR13.3 (NC), K13.4 (NC)
R13_NO: JR13.2 (NO), K13.3 (NO)
R14_COM: JR14.1 (COM), K14.2 (COM)
R14_NC: JR14.3 (NC), K14.4 (NC)
R14_NO: JR14.2 (NO), K14.3 (NO)
R15_COM: JR15.1 (COM), K15.2 (COM)
R15_NC: JR15.3 (NC), K15.4 (NC)
R15_NO: JR15.2 (NO), K15.3 (NO)
R16_COM: JR16.1 (COM), K16.2 (COM)
R16_NC: JR16.3 (NC), K16.4 (NC)
R16_NO: JR16.2 (NO), K16.3 (NO)
RELAY1_COIL_LOW: K1.5 (COIL-), U1.18 (RELAY1_COIL_LOW)
RELAY2_COIL_LOW: K2.5 (COIL-), U1.17 (RELAY2_COIL_LOW)
RELAY3_COIL_LOW: K3.5 (COIL-), U1.16 (RELAY3_COIL_LOW)
RELAY4_COIL_LOW: K4.5 (COIL-), U1.15 (RELAY4_COIL_LOW)
RELAY5_COIL_LOW: K5.5 (COIL-), U1.14 (RELAY5_COIL_LOW)
RELAY6_COIL_LOW: K6.5 (COIL-), U1.13 (RELAY6_COIL_LOW)
RELAY7_COIL_LOW: K7.5 (COIL-), U1.12 (RELAY7_COIL_LOW)
RELAY8_COIL_LOW: K8.5 (COIL-), U1.11 (RELAY8_COIL_LOW)
RELAY9_COIL_LOW: K9.5 (COIL-), U2.18 (RELAY9_COIL_LOW)
RELAY10_COIL_LOW: K10.5 (COIL-), U2.17 (RELAY10_COIL_LOW)
RELAY11_COIL_LOW: K11.5 (COIL-), U2.16 (RELAY11_COIL_LOW)
RELAY12_COIL_LOW: K12.5 (COIL-), U2.15 (RELAY12_COIL_LOW)
RELAY13_COIL_LOW: K13.5 (COIL-), U2.14 (RELAY13_COIL_LOW)
RELAY14_COIL_LOW: K14.5 (COIL-), U2.13 (RELAY14_COIL_LOW)
RELAY15_COIL_LOW: K15.5 (COIL-), U2.12 (RELAY15_COIL_LOW)
RELAY16_COIL_LOW: K16.5 (COIL-), U2.11 (RELAY16_COIL_LOW)
SD_CLK: J_SD.5 (SD_CLK), U4.3 (SD_CLK)
SD_CMD: J_SD.3 (SD_CMD), U4.6 (SD_CMD)
SD_CS: J_SD.2 (SD_CS), RSD1.2 (SD_CS), U4.8 (SD_CS)
SD_DAT1: J_SD.8 (SD_DAT1), RSD3.2 (SD_DAT1)
SD_DAT2: J_SD.1 (SD_DAT2), RSD4.2 (SD_DAT2)
TRAM_B_NEG: J_TRAMONTO.4 (TRAM_B_NEG), Q6.2 (D)
TRAM_G_NEG: J_TRAMONTO.3 (TRAM_G_NEG), Q5.2 (D)
TRAM_R_NEG: J_TRAMONTO.2 (TRAM_R_NEG), Q4.2 (D)

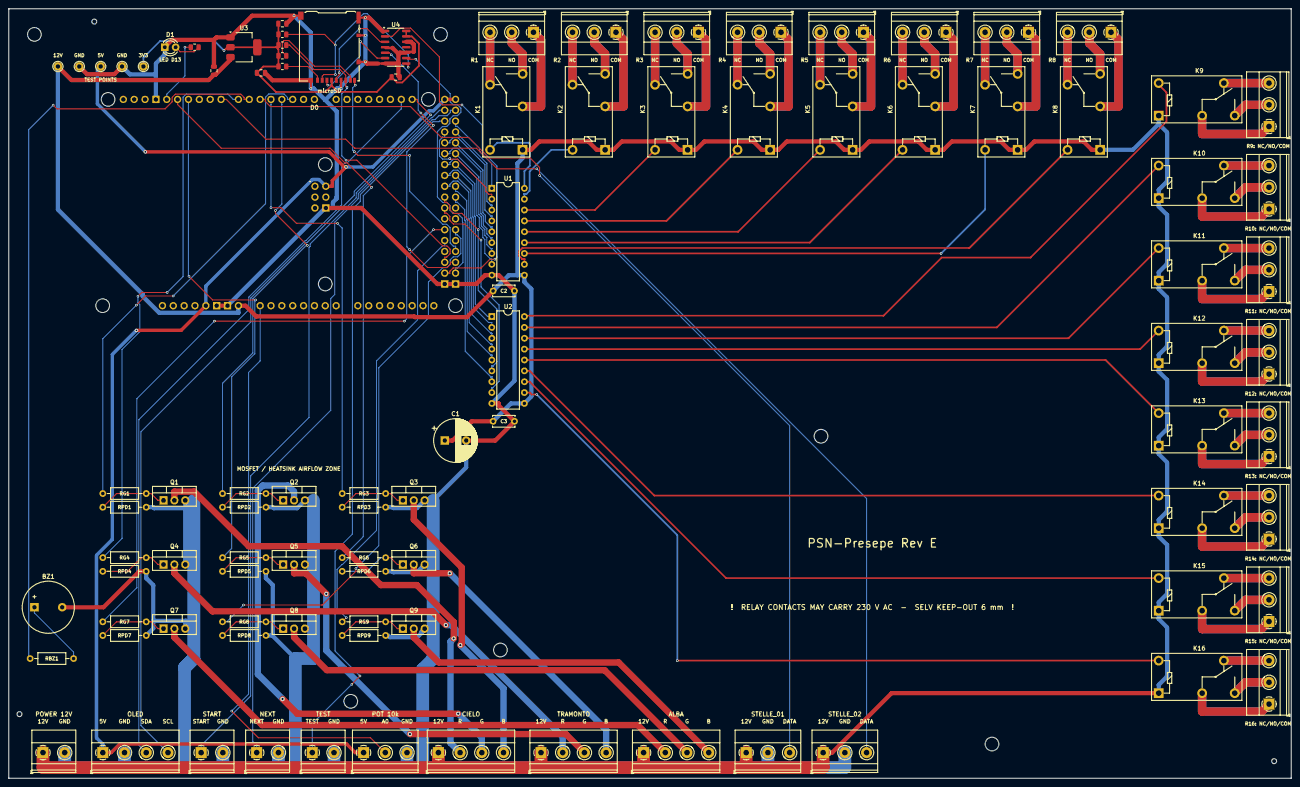
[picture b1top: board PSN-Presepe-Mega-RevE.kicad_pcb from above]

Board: 2 copper layers, 300.0 x 180.0 mm, 105 parts (0 on the bottom side), 133 nets.

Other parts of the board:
H1, H2, H3, H4, H5, H6: M3_NPTH; MountingHole_3.2mm_M3
TH1, TH2, TH3: ToolingHole; ToolingHole_JLC_1.152mm_NPTH

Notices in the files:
README.md:
License: not chosen yet. Add a `LICENSE` file to define how PSN-Presepe may be reused.
